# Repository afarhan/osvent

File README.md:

# osvent
Open Source Ventilator Controller

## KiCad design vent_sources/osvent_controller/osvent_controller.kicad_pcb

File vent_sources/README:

These are the sources for an open source Ventilator that can be easily assembledfrom ordinary parts. The https://simulation.health.ufl.edu/

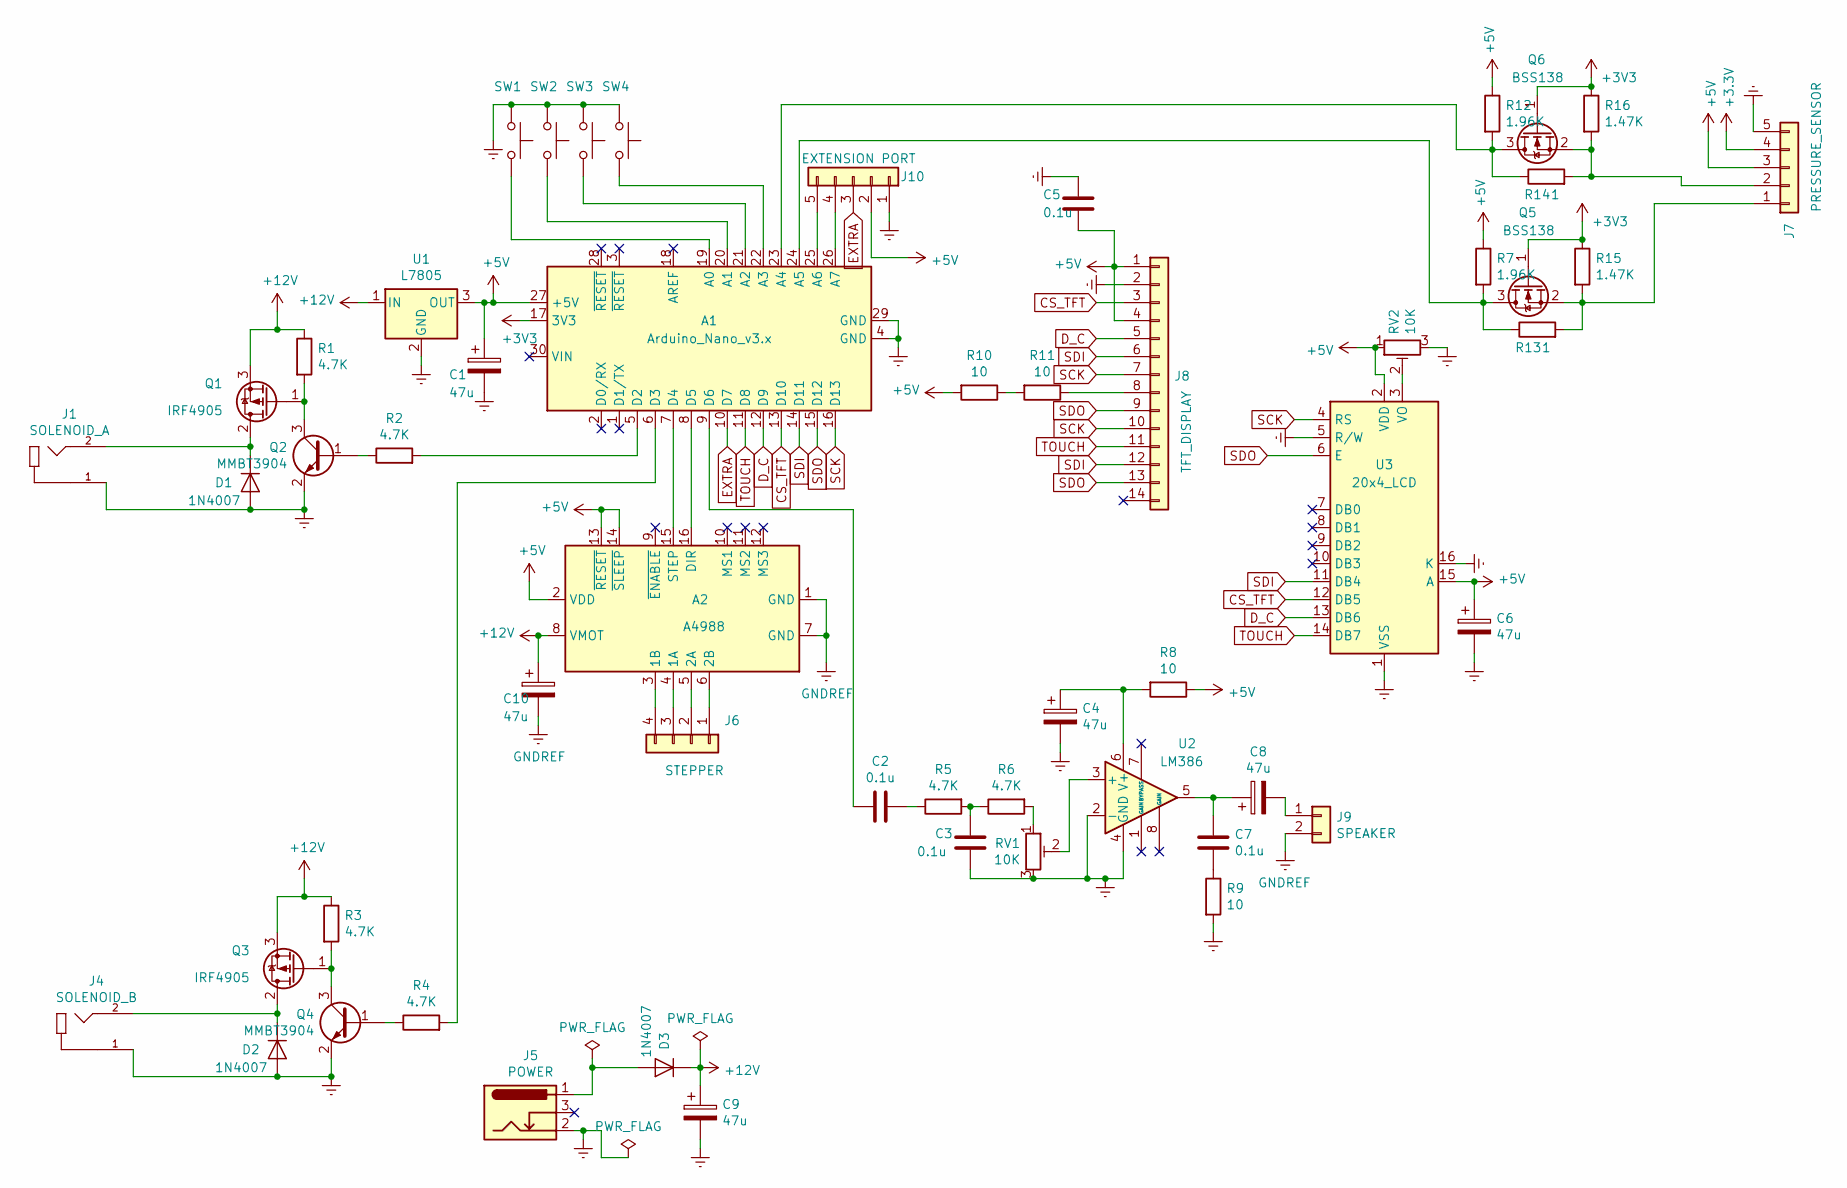
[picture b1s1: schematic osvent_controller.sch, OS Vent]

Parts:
A1: Arduino_Nano_v3.x; Arduino_Nano
A2: A4988; Pololu_Breakout-16_15.2x20.3mm
C1, C4, C6, C8, C9, C10: 47u; CP_Radial_D5.0mm_P2.50mm
C2, C3, C5: 0.1u; C_0805_2012Metric_Pad1.15x1.40mm_HandSolder
C7: 0.1u; CP_Radial_D5.0mm_P2.50mm
D1, D2, D3: 1N4007; D_SOD-123
J1: SOLENOID_A; Kycon_KLPX-0848A-2-x
J4: SOLENOID_B; Kycon_KLPX-0848A-2-x
J5: POWER; BarrelJack_Horizontal
J6: STEPPER; PinHeader_1x04_P2.54mm_Horizontal
J7: PRESSURE_SENSOR; PinHeader_1x05_P2.54mm_Horizontal
J8: TFT_DISPLAY; PinSocket_1x14_P2.54mm_Vertical
J9: SPEAKER; PinHeader_1x02_P2.54mm_Horizontal
J10: EXTENSION PORT; PinHeader_1x05_P2.54mm_Horizontal
Q1, Q3: IRF4905; TO-220-3_Vertical
Q2, Q4: MMBT3904; SOT-23
Q5, Q6: BSS138; SOT-23
R1, R2, R3, R4, R5, R6: 4.7K; R_0805_2012Metric_Pad1.15x1.40mm_HandSolder
R7, R12: 1.96K; R_0805_2012Metric_Pad1.15x1.40mm_HandSolder
R8, R9, R10, R11: 10; R_0805_2012Metric_Pad1.15x1.40mm_HandSolder
R13, R14: 1; R_0805_2012Metric_Pad1.15x1.40mm_HandSolder
R15, R16: 1.47K; R_0805_2012Metric_Pad1.15x1.40mm_HandSolder
RV1, RV2: 10K; Potentiometer_Bourns_3386P_Vertical
SW1, SW2, SW3, SW4: SW_Push; SW_PUSH_6mm_H13mm
U1: L7805; TO-220-3_Vertical
U2: LM386; DIP-8_W7.62mm_LongPads
U3: 20x4_LCD; WC1602A

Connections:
+5V: A1.27 (+5V), A2.2 (VDD), A2.13 (~RESET), A2.14 (~SLEEP), C1.1, C5.2, C6.1, J7.3, J8.1, J8.4, J10.2, R7.1, R8.1, R10.2, R12.1, RV2.1, U1.3 (OUT), U3.2 (VDD), U3.15 (A)
+12V: A2.8 (VMOT), C9.1, C10.1, D3.1 (K), Q1.3 (S), Q3.3 (S), R1.1, R3.1, U1.1 (IN)
CS_TFT: A1.13 (D10), J8.3, U3.12 (DB5)
D_C: A1.12 (D9), J8.5, U3.13 (DB6)
EXTRA: A1.10 (D7), J10.3
GNDREF: A1.4 (GND), A1.29 (GND), A2.1 (GND), A2.7 (GND), C1.2, C3.2, C4.2, C5.1, C6.2, C9.2, C10.2, D1.2 (A), D2.2 (A), J1.1, J4.1, J5.2, J7.5, J8.2, J9.2, J10.1, Q2.2 (E), Q4.2 (E), R9.2, RV1.3, RV2.3, SW1.1, SW2.1, SW3.1, SW4.1, U1.2 (GND), U2.2 (-), U2.4 (GND), U3.1 (VSS), U3.5 (R/W), U3.16 (K)
unnamed: A1.5 (D2), R2.2
unnamed: A1.6 (D3), R4.2
unnamed: A1.7 (D4), A2.15 (STEP)
unnamed: A1.8 (D5), A2.16 (DIR)
unnamed: A1.9 (D6), C2.2
unnamed: A1.19 (A0), SW1.2
unnamed: A1.20 (A1), SW2.2
unnamed: A1.21 (A2), SW3.2
unnamed: A1.22 (A3), SW4.2
unnamed: A1.23 (A4), Q6.3 (D), R12.2, R14.1
unnamed: A1.24 (A5), Q5.3 (D), R7.2, R13.1
unnamed: A1.25 (A6), J10.5
unnamed: A1.26 (A7), J10.4
unnamed: A2.3 (1B), J6.4
unnamed: A2.4 (1A), J6.3
unnamed: A2.5 (2A), J6.2
unnamed: A2.6 (2B), J6.1
unnamed: C2.1, R5.1
unnamed: C3.1, R5.2, R6.1
unnamed: C4.1, R8.2, U2.6 (V+)
unnamed: C7.1, C8.1, U2.5
unnamed: C7.2, R9.1
unnamed: C8.2, J9.1
unnamed: D1.1 (K), J1.2, Q1.2 (D)
unnamed: D2.1 (K), J4.2, Q3.2 (D)
unnamed: D3.2 (A), J5.1
unnamed: J7.1, Q5.2 (S), R13.2, R15.2
unnamed: J7.2, Q6.2 (S), R14.2, R16.2
unnamed: J8.8, R11.1
unnamed: Q1.1 (G), Q2.3 (C), R1.2
unnamed: Q2.1 (B), R2.1
unnamed: Q3.1 (G), Q4.3 (C), R3.2
unnamed: Q4.1 (B), R4.1
unnamed: R6.2, RV1.1
unnamed: R10.1, R11.2
unnamed: RV1.2, U2.3 (+)
unnamed: RV2.2, U3.3 (VO)
SCK: A1.16 (D13), J8.7, J8.10, U3.4 (RS)
SDI: A1.14 (D11), J8.6, J8.12, U3.11 (DB4)
SDO: A1.15 (D12), J8.9, J8.13, U3.6 (E)
TOUCH: A1.11 (D8), J8.11, U3.14 (DB7)

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
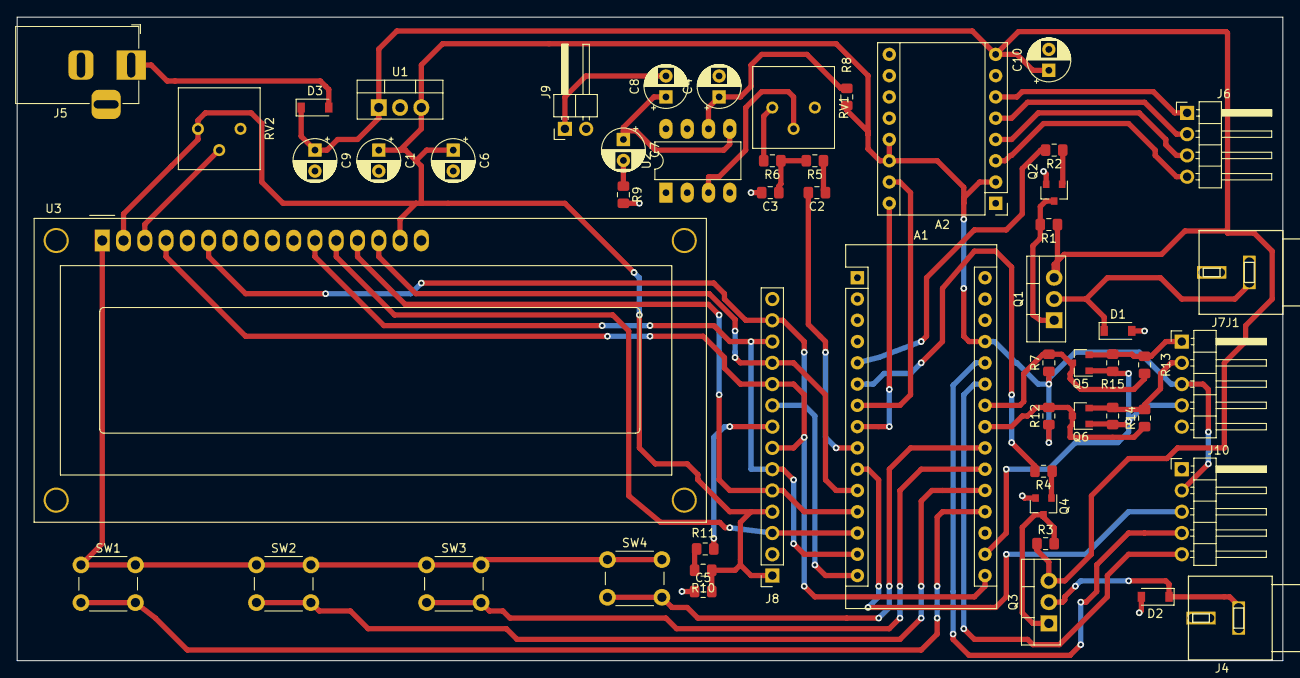
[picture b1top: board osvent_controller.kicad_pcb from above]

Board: 2 copper layers, 151.1 x 76.8 mm, 54 parts (0 on the bottom side), 48 nets.

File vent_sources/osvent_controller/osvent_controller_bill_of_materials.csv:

"Id";"Designator";"Package";"Quantity";"Designation";"Supplier and ref";
1;"C10,C6,C8,C9,C4,C1";"CP_Radial_D5.0mm_P2.50mm";6;"47u";;;
2;"J10";"PinHeader_1x05_P2.54mm_Horizontal";1;"EXTENSION PORT";;;
3;"SW1,SW4,SW3,SW2";"SW_PUSH_6mm_H13mm";4;"SW_Push";;;
4;"J1";"Kycon_KLPX-0848A-2-x";1;"SOLENOID_A";;;
5;"J4";"Kycon_KLPX-0848A-2-x";1;"SOLENOID_B";;;
6;"C7";"CP_Radial_D5.0mm_P2.50mm";1;"0.1u";;;
7;"R16,R15";"R_0805_2012Metric_Pad1.15x1.40mm_HandSolder";2;"1.47K";;;
8;"R14,R13";"R_0805_2012Metric_Pad1.15x1.40mm_HandSolder";2;"1";;;
9;"R12,R7";"R_0805_2012Metric_Pad1.15x1.40mm_HandSolder";2;"1.96K";;;
10;"Q6,Q5";"SOT-23";2;"BSS138";;;
11;"U3";"WC1602A";1;"20x4_LCD";;;
12;"A1";"Arduino_Nano";1;"Arduino_Nano_v3.x";;;
13;"Q4,Q2";"SOT-23";2;"MMBT3904";;;
14;"R1,R4,R3,R2,R6,R5";"R_0805_2012Metric_Pad1.15x1.40mm_HandSolder";6;"4.7K";;;
15;"D1,D2,D3";"D_SOD-123";3;"1N4007";;;
16;"Q1,Q3";"TO-220-3_Vertical";2;"IRF4905";;;
17;"J6";"PinHeader_1x04_P2.54mm_Horizontal";1;"STEPPER";;;
18;"J7";"PinHeader_1x05_P2.54mm_Horizontal";1;"PRESSURE_SENSOR";;;
19;"RV2,RV1";"Potentiometer_Bourns_3386P_Vertical";2;"10K";;;
20;"J5";"BarrelJack_Horizontal";1;"POWER";;;
21;"U2";"DIP-8_W7.62mm_LongPads";1;"LM386";;;
22;"U1";"TO-220-3_Vertical";1;"L7805";;;
23;"R11,R10,R9,R8";"R_0805_2012Metric_Pad1.15x1.40mm_HandSolder";4;"10";;;
24;"J9";"PinHeader_1x02_P2.54mm_Horizontal";1;"SPEAKER";;;
25;"J8";"PinSocket_1x14_P2.54mm_Vertical";1;"TFT_DISPLAY";;;
26;"C5,C3,C2";"C_0805_2012Metric_Pad1.15x1.40mm_HandSolder";3;"0.1u";;;
27;"A2";"Pololu_Breakout-16_15.2x20.3mm";1;"A4988";;;

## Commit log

2020-03-30 Initial commit
    These are the PCB and the source files for the OSVent Controller
2020-03-30 Flipped the RCA connectors around
2020-03-31 Removed relays, added extra connector, surge cap
    1. Removed the PCB mounted relays. Instead use outboard relays of appropriate rating.
    2. Added a 47uf close to A4988 to protect from ESD/surge
    3. Added a new connector with A6,A7, D7, +5 and ground for analog sensors

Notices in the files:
vent_sources/osvent_controller/osvent_controller.sch:
Released under GPL v3.
